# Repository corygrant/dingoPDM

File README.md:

## dingoPDM
dingoPDM is an Infineon Profet based Power Distribution Module. 

# [**Documentation**](https://corygrant.github.io/dingoElec/dingopdm/introduction/)

# [**Store**](https://dingo-electronics.square.site/product/dingopdm/1)

## Disclaimer
Please note that this product has been designed by a hobbyist, not a professional. It is intended for off-road and testing use only. Users should operate the product at their own discretion and risk. The designer explicitly disclaims any responsibility for damage or injury that may result from the use of this product.

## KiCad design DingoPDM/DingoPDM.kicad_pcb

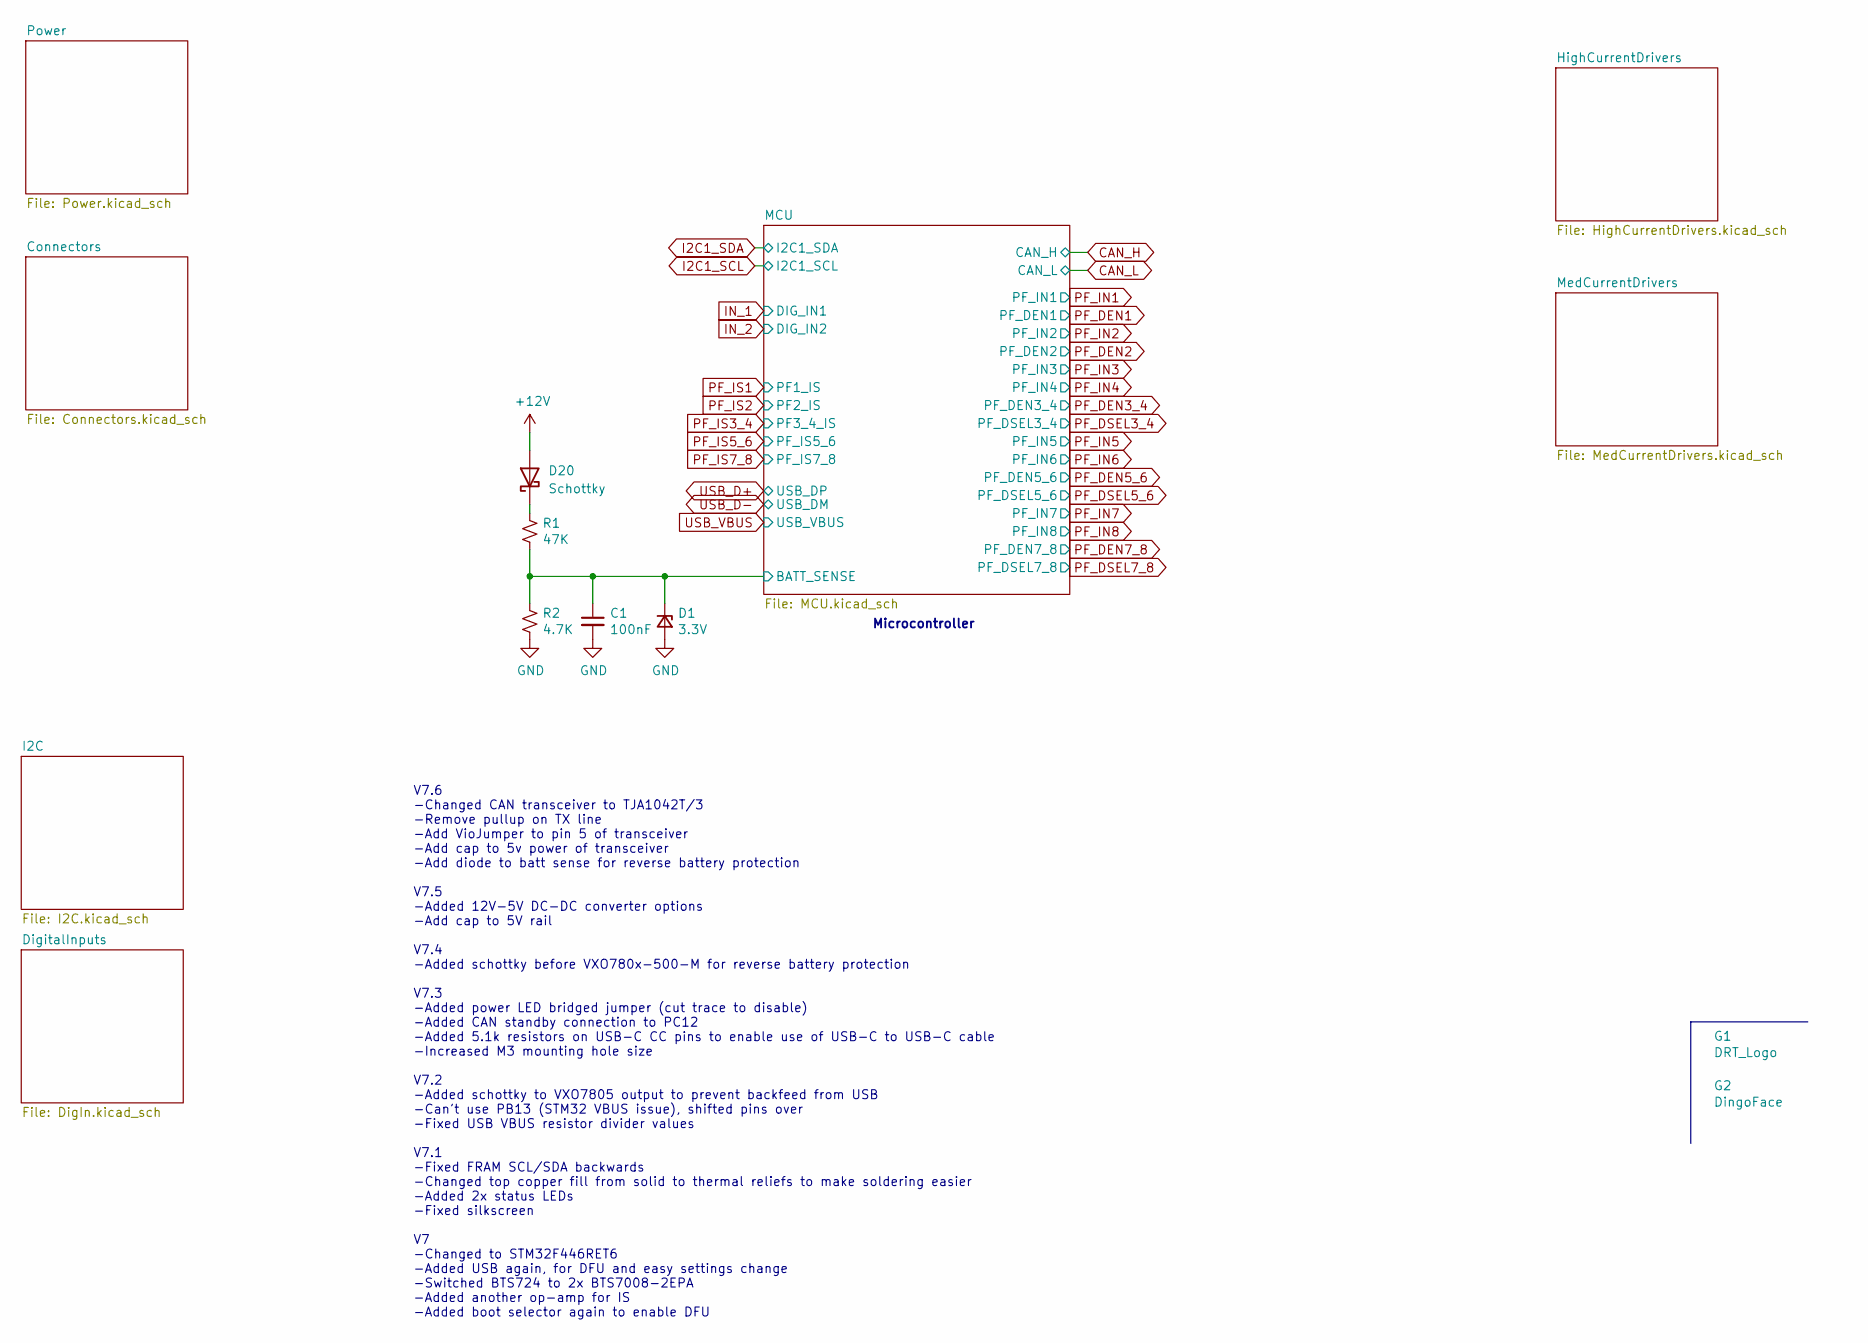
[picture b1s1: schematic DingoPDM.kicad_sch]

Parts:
C1: 100nF; C_0805_2012Metric; Digi-Key_PN 478-1395-1-ND
D1: 3.3V; D_SOD-323_HandSoldering; Digi-Key_PN 1727-5150-1-ND
D20: Schottky; D_SOD-123; Digi-Key_PN 1727-2394-1-ND
G1: DRT_Logo; DRTLogo
G2: DingoFace; DingoFaceNoFill
R1: 47K; R_0805_2012Metric; Digi-Key_PN 311-47.0KCRCT-ND
R2: 4.7K; R_0805_2012Metric; Digi-Key_PN 311-4.70KCRCT-ND

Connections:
+12V: D20.2 (A); also elsewhere on the board
/MCU/BATT_SENSE: C1.1, D1.1 (K), R1.2, R2.1; also elsewhere on the board
GND: C1.2, D1.2 (A), R2.2; also elsewhere on the board
unnamed: D20.1 (K), R1.1

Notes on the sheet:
Microcontroller
V7.6 -Changed CAN transceiver to TJA1042T/3 -Remove pullup on TX line -Add VioJumper to pin 5 of transceiver -Add cap to 5v power of transceiver -Add diode to batt sense for reverse battery protection V7.5 -Added 12V-5V DC-DC converter options -Add cap to 5V rail V7.4 -Added schottky before VXO780x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

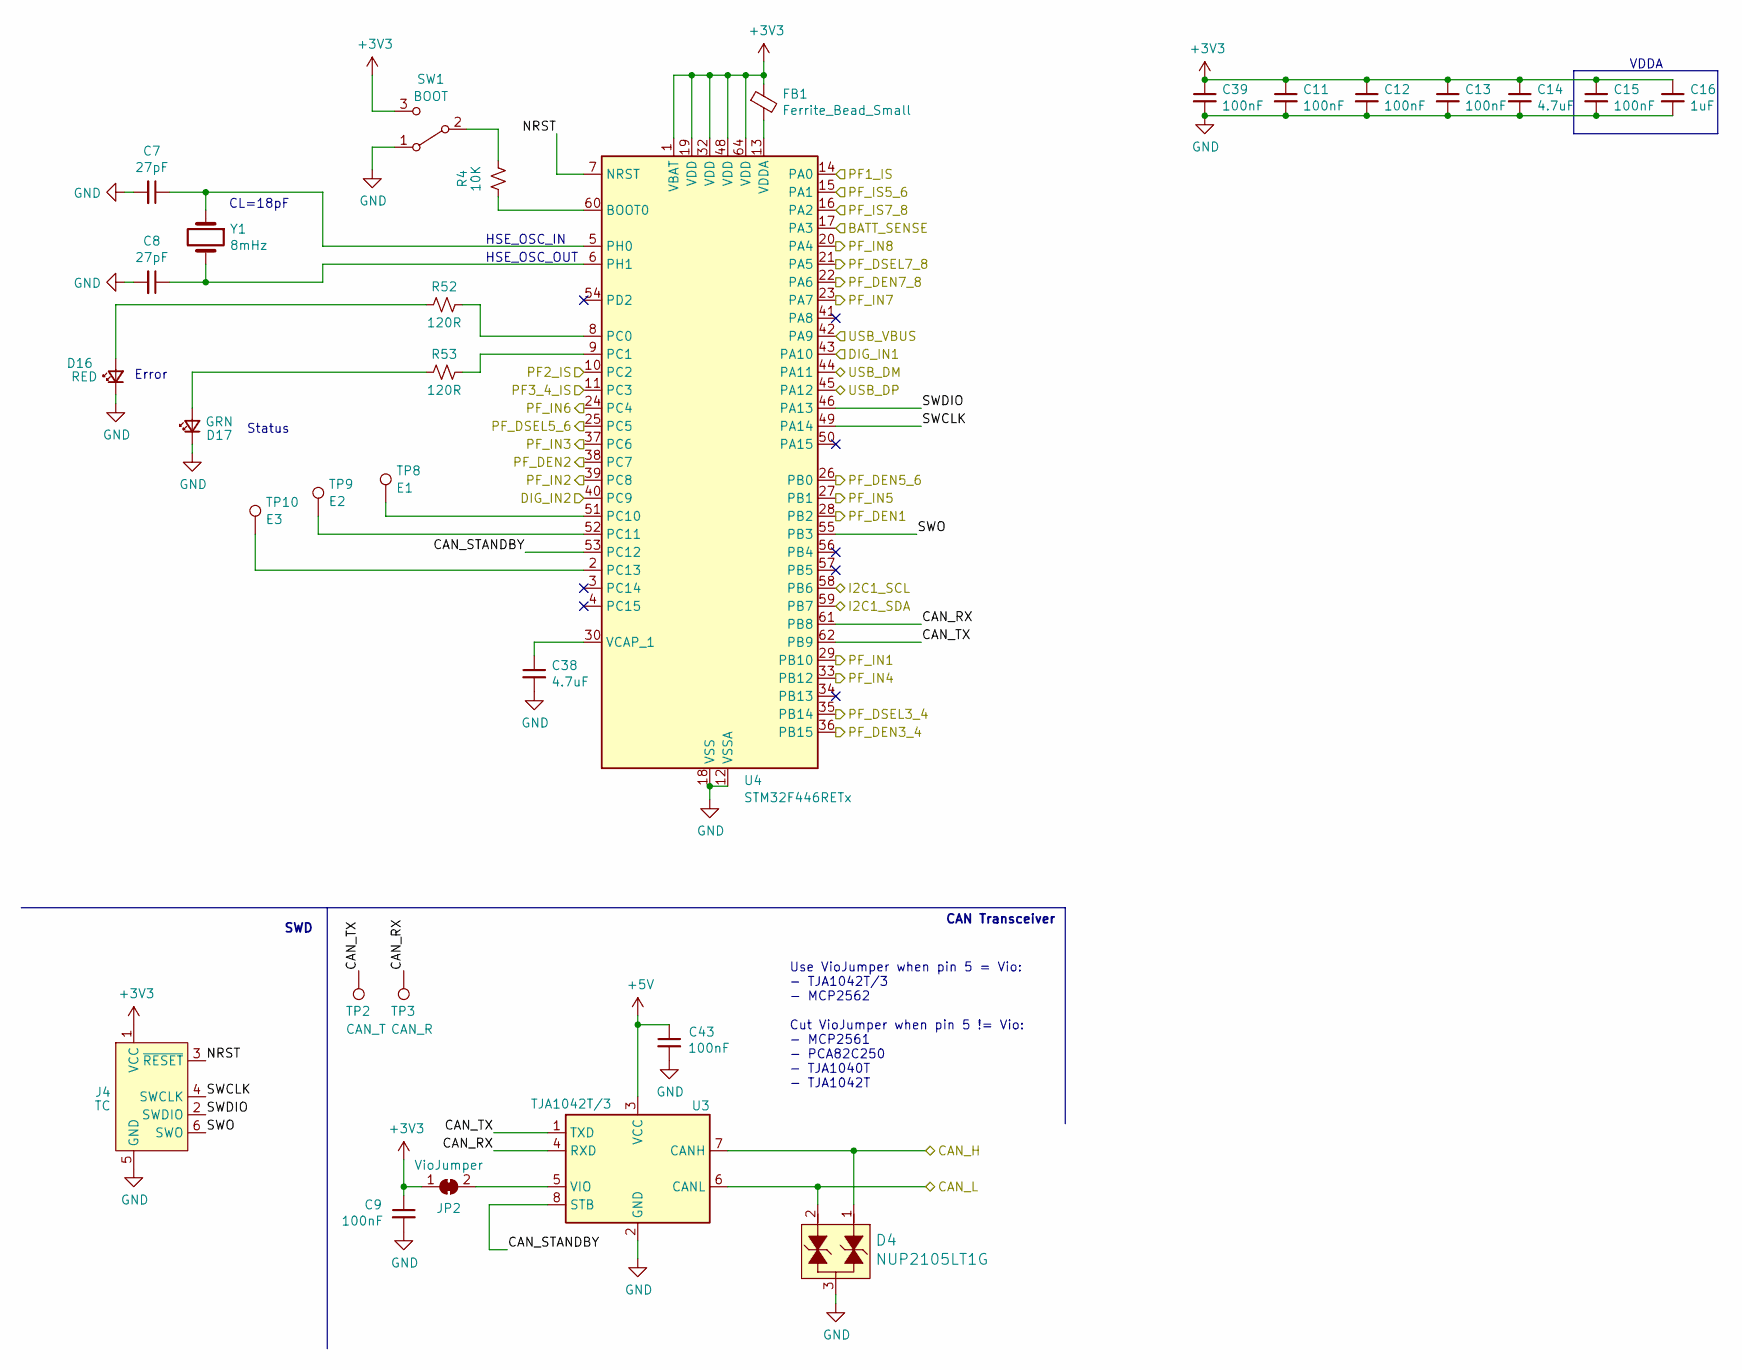
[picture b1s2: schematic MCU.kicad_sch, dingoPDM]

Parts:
C7, C8: 27pF; C_0805_2012Metric; Digi-Key_PN 478-10518-1-ND
C9, C11, C12, C13, C15, C39, C43: 100nF; C_0805_2012Metric; Digi-Key_PN 478-1395-1-ND
C14, C38: 4.7uF; C_0805_2012Metric; Digi-Key_PN 1276-2873-1-ND
C16: 1uF; C_0805_2012Metric; Digi-Key_PN 311-1365-1-ND
D4: NUP2105LT1G; SOT-23-3; Digi-Key_PN NUP2105LT1GOSCT-ND
D16: RED; LED_0805_2012Metric; Digi-Key_PN 475-1278-1-ND
D17: GRN; LED_0805_2012Metric; Digi-Key_PN 475-1410-1-ND
FB1: Ferrite_Bead_Small; R_0805_2012Metric; Digi-Key_PN 490-1054-1-ND
J4: TC; Tag-Connect_TC2030-IDC-NL_2x03_P1.27mm_Vertical
JP2: VioJumper; SolderJumper-2_P1.3mm_Bridged_RoundedPad1.0x1.5mm
R4: 10K; R_0805_2012Metric; Digi-Key_PN 311-10.0KCRDKR-ND
R52, R53: 120R; R_0805_2012Metric; Digi-Key_PN 311-120CRCT-ND
SW1: BOOT; CJS-1200TB; Digi-Key_PN 563-CJS-1200TB1CT-ND
TP2: CAN_T; TestPoint_Keystone_5000-5004_Miniature
TP3: CAN_R; TestPoint_Keystone_5000-5004_Miniature
TP8: E1; TestPoint_Keystone_5000-5004_Miniature
TP9: E2; TestPoint_Keystone_5000-5004_Miniature
TP10: E3; TestPoint_Keystone_5000-5004_Miniature
U3: TJA1042T/3; SOIC-8_3.9x4.9mm_P1.27mm; Digi-Key_PN 568-12625-1-ND
U4: STM32F446RETx; LQFP-64_10x10mm_P0.5mm; Digi-Key_PN 497-15376-ND
Y1: 8mHz; Crystal_SMD_5032-2Pin_5.0x3.2mm_HandSoldering; Digi-Key_PN 535-10630-1-ND

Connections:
+3V3: C9.1, C11.1, C12.1, C13.1, C14.1, C15.1, C16.1, C39.1, FB1.1, J4.1 (VCC), JP2.1 (A), SW1.3 (C), U4.1 (VBAT), U4.19 (VDD), U4.32 (VDD), U4.48 (VDD), U4.64 (VDD); also elsewhere on the board
+5V: C43.1, U3.3 (VCC); also elsewhere on the board
/MCU/BATT_SENSE: U4.17 (PA3); also elsewhere on the board
/MCU/CAN_RX: TP3.1, U3.4 (RXD), U4.61 (PB8)
/MCU/CAN_STANDBY: U3.8 (STB), U4.53 (PC12)
/MCU/CAN_TX: TP2.1, U3.1 (TXD), U4.62 (PB9)
/MCU/NRST: J4.3 (~RESET), U4.7 (NRST)
/MCU/SWCLK: J4.4 (SWCLK), U4.49 (PA14)
/MCU/SWDIO: J4.2 (SWDIO), U4.46 (PA13)
/MCU/SWO: J4.6 (SWO), U4.55 (PB3)
CAN_H: D4.1, U3.7 (CANH); also elsewhere on the board
CAN_L: D4.2, U3.6 (CANL); also elsewhere on the board
GND: C7.2, C8.2, C9.2, C11.2, C12.2, C13.2, C14.2, C15.2, C16.2, C38.2, C39.2, C43.2, D4.3, D16.1 (K), D17.1 (K), J4.5 (GND), SW1.1 (A), U3.2 (GND), U4.12 (VSSA), U4.18 (VSS), U4.31 (VSS), U4.47 (VSS), U4.63 (VSS); also elsewhere on the board
I2C1_SCL: U4.58 (PB6); also elsewhere on the board
I2C1_SDA: U4.59 (PB7); also elsewhere on the board
IN_1: U4.43 (PA10); also elsewhere on the board
IN_2: U4.40 (PC9); also elsewhere on the board
unnamed: D16.2 (A), R52.2
unnamed: D17.2 (A), R53.2
unnamed: JP2.2 (B), U3.5 (VIO)
unnamed: R4.1, SW1.2 (B)
unnamed: R4.2, U4.60 (BOOT0)
unnamed: R52.1, U4.8 (PC0)
unnamed: R53.1, U4.9 (PC1)
unnamed: TP8.1, U4.51 (PC10)
unnamed: TP9.1, U4.52 (PC11)
unnamed: TP10.1, U4.2 (PC13)
unnamed: C7.1, U4.5 (PH0), Y1.1
unnamed: C8.1, U4.6 (PH1), Y1.2
unnamed: C38.1, U4.30 (VCAP_1)
unnamed: FB1.2, U4.13 (VDDA)
PF_DEN1: U4.28 (PB2); also elsewhere on the board
PF_DEN2: U4.38 (PC7); also elsewhere on the board
PF_DEN3_4: U4.36 (PB15); also elsewhere on the board
PF_DEN5_6: U4.26 (PB0); also elsewhere on the board
PF_DEN7_8: U4.22 (PA6); also elsewhere on the board
PF_DSEL3_4: U4.35 (PB14); also elsewhere on the board
PF_DSEL5_6: U4.25 (PC5); also elsewhere on the board
PF_DSEL7_8: U4.21 (PA5); also elsewhere on the board
PF_IN1: U4.29 (PB10); also elsewhere on the board
PF_IN2: U4.39 (PC8); also elsewhere on the board
PF_IN3: U4.37 (PC6); also elsewhere on the board
PF_IN4: U4.33 (PB12); also elsewhere on the board
PF_IN5: U4.27 (PB1); also elsewhere on the board
PF_IN6: U4.24 (PC4); also elsewhere on the board
PF_IN7: U4.23 (PA7); also elsewhere on the board
PF_IN8: U4.20 (PA4); also elsewhere on the board
PF_IS1: U4.14 (PA0); also elsewhere on the board
PF_IS2: U4.10 (PC2); also elsewhere on the board
PF_IS3_4: U4.11 (PC3); also elsewhere on the board
PF_IS5_6: U4.15 (PA1); also elsewhere on the board
PF_IS7_8: U4.16 (PA2); also elsewhere on the board
USB_D+: U4.45 (PA12); also elsewhere on the board
USB_D-: U4.44 (PA11); also elsewhere on the board
USB_VBUS: U4.42 (PA9); also elsewhere on the board

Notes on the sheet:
Use VioJumper when pin 5 = Vio: - TJA1042T/3 - MCP2562 Cut VioJumper when pin 5 != Vio: - MCP2561 - PCA82C250 - TJA1040T - TJA1042T
SWD
Error
CAN Transceiver
HSE_OSC_IN
CL=18pF
HSE_OSC_OUT
VDDA
Status

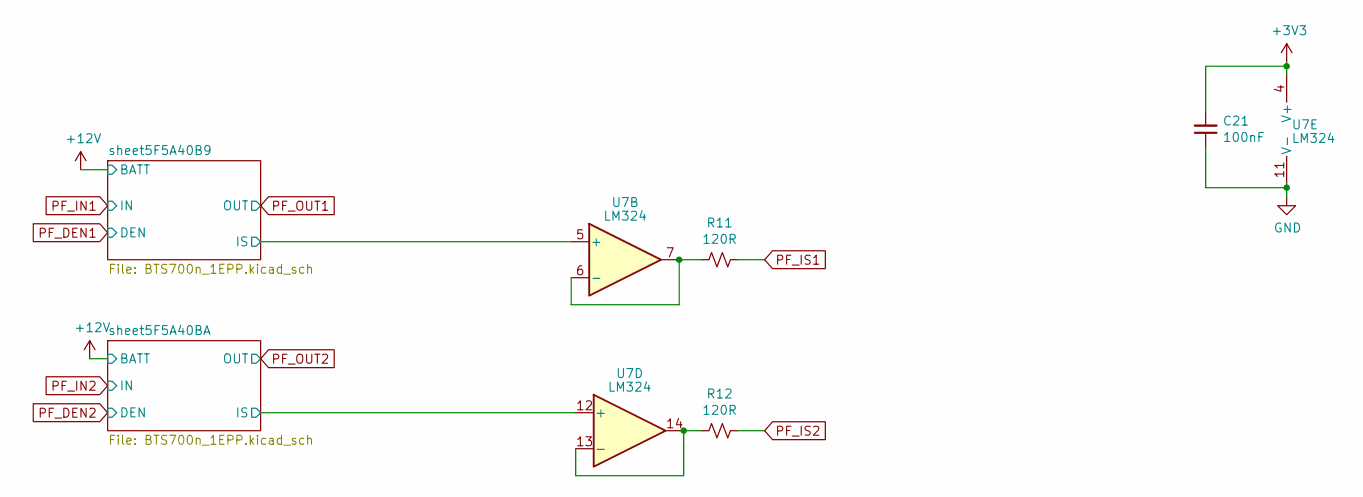
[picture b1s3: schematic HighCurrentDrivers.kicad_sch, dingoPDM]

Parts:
C21: 100nF; C_0805_2012Metric; Digi-Key_PN 478-1395-1-ND
R11, R12: 120R; R_0805_2012Metric; Digi-Key_PN 311-120CRCT-ND
U7: LM324; TSSOP-14_4.4x5mm_P0.65mm; Digi-Key_PN 497-7330-1-ND

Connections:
+3V3: C21.2, U7.4 (V+); also elsewhere on the board
/HighCurrentDrivers/sheet5F5A40B9/IS: U7.5 (+); also elsewhere on the board
/HighCurrentDrivers/sheet5F5A40BA/IS: U7.12 (+); also elsewhere on the board
GND: C21.1, U7.11 (V-); also elsewhere on the board
unnamed: R11.2, U7.6 (-), U7.7
unnamed: R12.2, U7.13 (-), U7.14
PF_IS1: R11.1; also elsewhere on the board
PF_IS2: R12.1; also elsewhere on the board

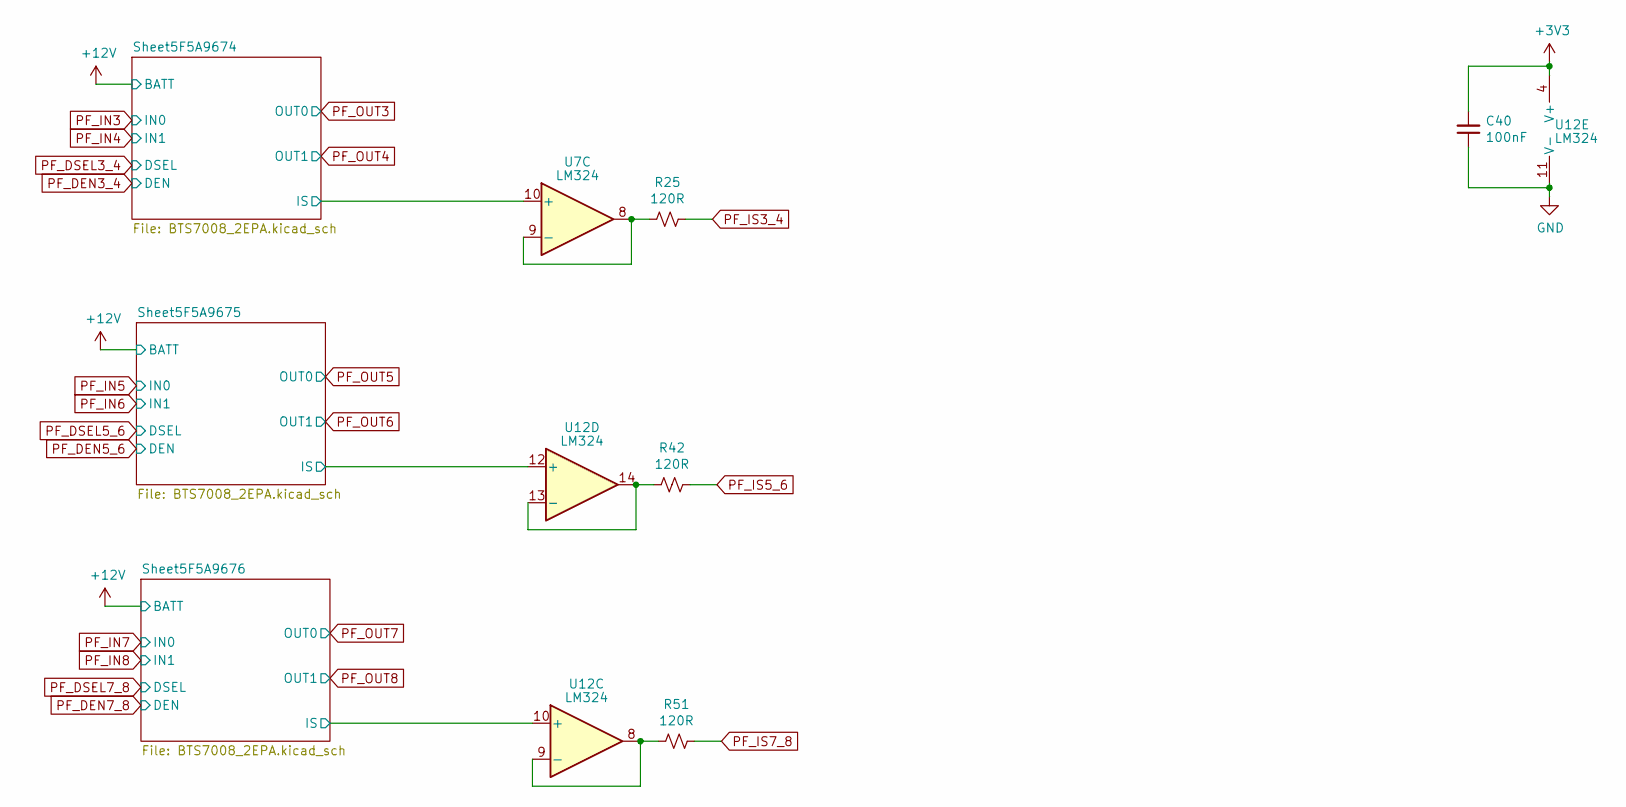
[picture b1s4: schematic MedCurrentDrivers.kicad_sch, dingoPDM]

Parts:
C40: 100nF; C_0805_2012Metric; Digi-Key_PN 478-1395-1-ND
R25, R42, R51: 120R; R_0805_2012Metric; Digi-Key_PN 311-120CRCT-ND
U7, U12: LM324; TSSOP-14_4.4x5mm_P0.65mm; Digi-Key_PN 497-7330-1-ND

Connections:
+3V3: C40.2, U12.4 (V+); also elsewhere on the board
/MedCurrentDrivers/Sheet5F5A9674/IS: U7.10 (+); also elsewhere on the board
/MedCurrentDrivers/Sheet5F5A9675/IS: U12.12 (+); also elsewhere on the board
/MedCurrentDrivers/Sheet5F5A9676/IS: U12.10 (+); also elsewhere on the board
GND: C40.1, U12.11 (V-); also elsewhere on the board
unnamed: R25.2, U7.8, U7.9 (-)
unnamed: R51.2, U12.8, U12.9 (-)
unnamed: R42.2, U12.13 (-), U12.14
PF_IS3_4: R25.1; also elsewhere on the board
PF_IS5_6: R42.1; also elsewhere on the board
PF_IS7_8: R51.1; also elsewhere on the board

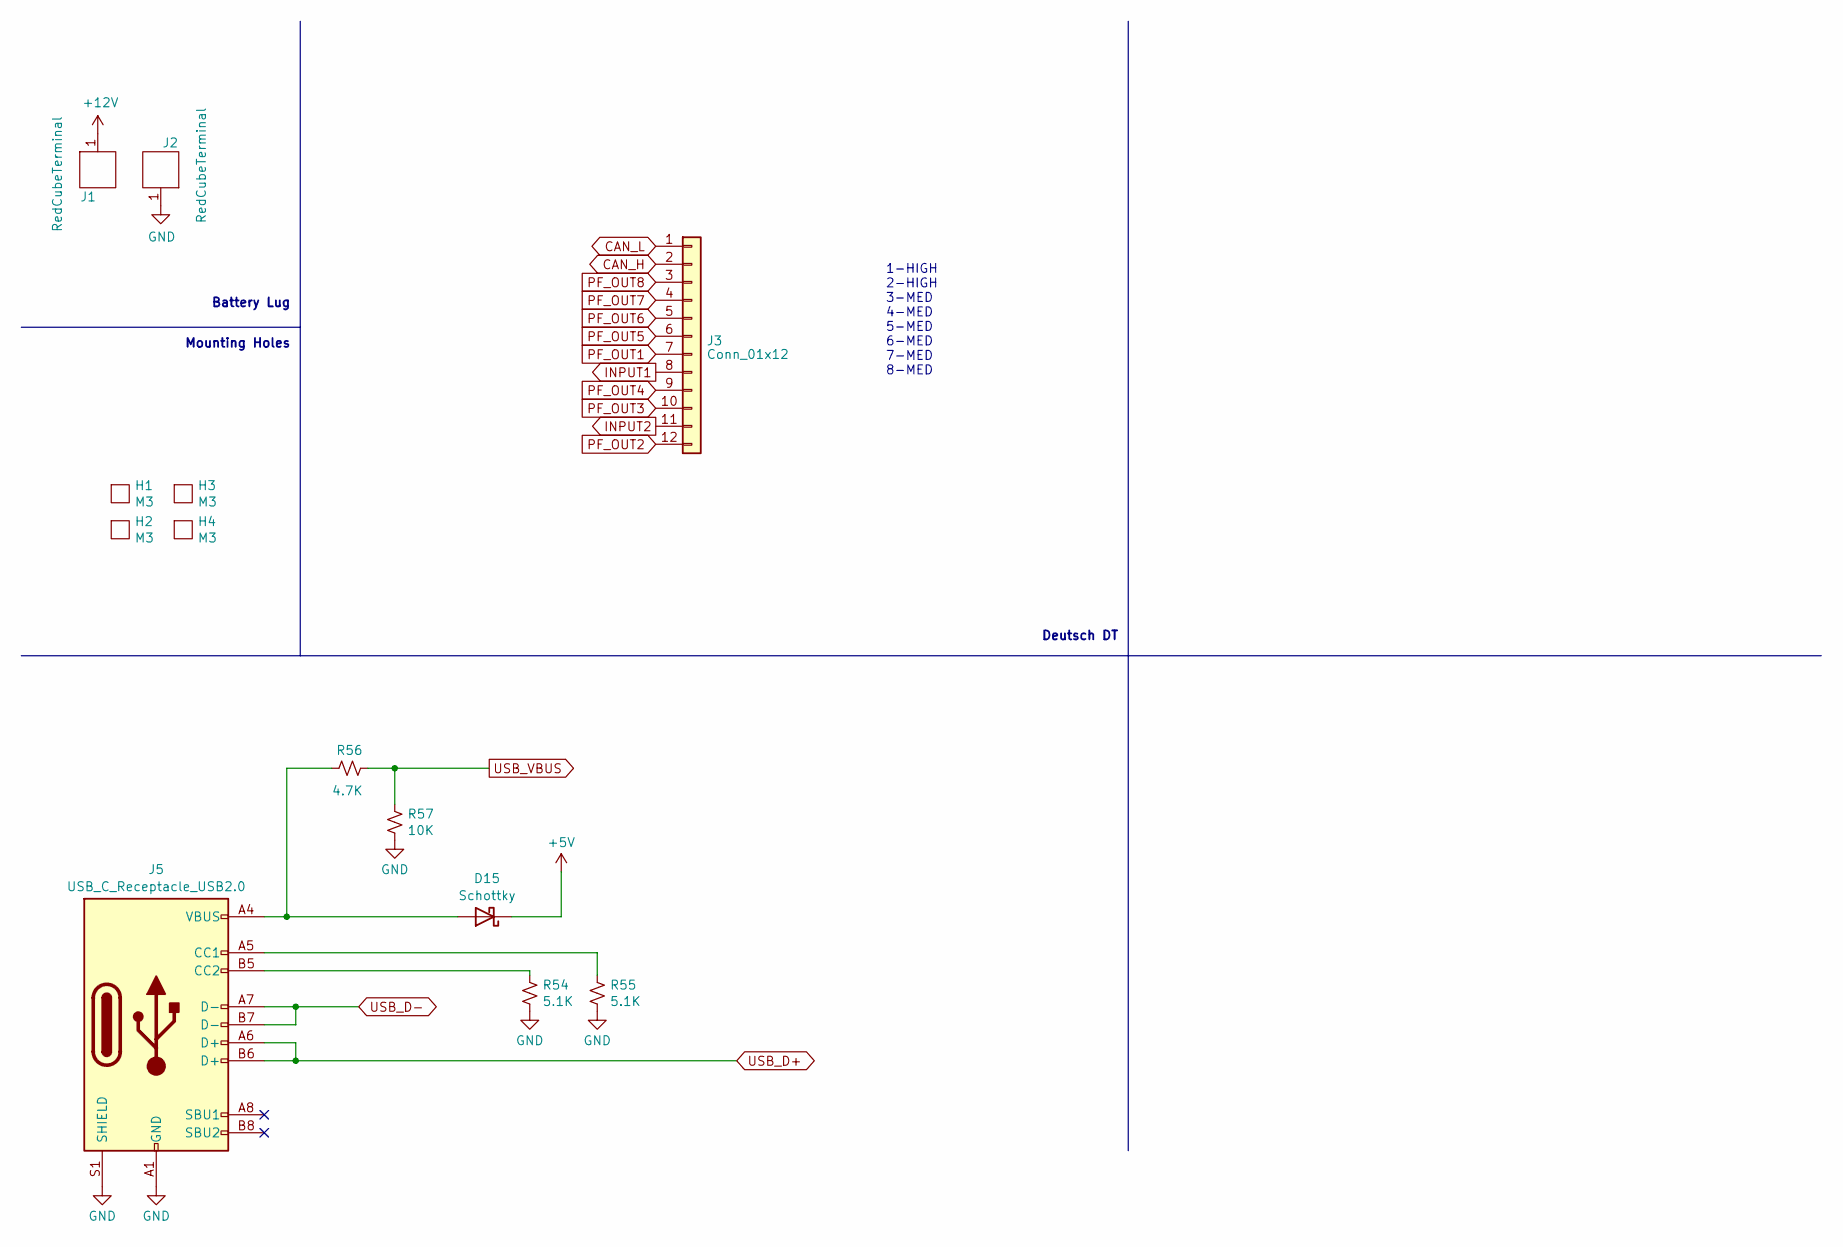
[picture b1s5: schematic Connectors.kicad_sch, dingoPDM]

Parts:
D15: Schottky; D_SOD-123; Digi-Key_PN 1727-2394-1-ND
H1, H2, H3, H4: M3; MountingHole_3.2mm_M3_ISO7380_Pad
J1, J2: RedCubeTerminal; M6_Hole_8Pin_7461084; Digi-Key_PN 732-3203-ND
J3: Conn_01x12; DT15-12PA; LCSC C5341788
J5: USB_C_Receptacle_USB2.0; USB_C_Receptacle_GCT_USB4085; Digi-Key_PN 2073-USB4085-GF-ACT-ND
R54, R55: 5.1K; R_0805_2012Metric; Digi-Key_PN 311-5.1KARCT-ND
R56: 4.7K; R_0805_2012Metric; Digi-Key_PN 311-4.70KCRCT-ND
R57: 10K; R_0805_2012Metric; Digi-Key_PN 311-10.0KCRDKR-ND

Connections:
+5V: D15.1 (K); also elsewhere on the board
+12V: J1.1; also elsewhere on the board
CAN_H: J3.2; also elsewhere on the board
CAN_L: J3.1; also elsewhere on the board
GND: J2.1, J5.A1 (GND), J5.A12 (GND), J5.B1 (GND), J5.B12 (GND), J5.S1 (SHIELD), R54.2, R55.2, R57.2; also elsewhere on the board
INPUT1: J3.8; also elsewhere on the board
INPUT2: J3.11; also elsewhere on the board
unnamed: D15.2 (A), J5.A4 (VBUS), J5.A9 (VBUS), J5.B4 (VBUS), J5.B9 (VBUS), R56.1
unnamed: J5.A5 (CC1), R55.1
unnamed: J5.B5 (CC2), R54.1
PF_OUT1: J3.7; also elsewhere on the board
PF_OUT2: J3.12; also elsewhere on the board
PF_OUT3: J3.10; also elsewhere on the board
PF_OUT4: J3.9; also elsewhere on the board
PF_OUT5: J3.6; also elsewhere on the board
PF_OUT6: J3.5; also elsewhere on the board
PF_OUT7: J3.4; also elsewhere on the board
PF_OUT8: J3.3; also elsewhere on the board
USB_D+: J5.A6 (D+), J5.B6 (D+); also elsewhere on the board
USB_D-: J5.A7 (D-), J5.B7 (D-); also elsewhere on the board
USB_VBUS: R56.2, R57.1; also elsewhere on the board

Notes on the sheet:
1-HIGH 2-HIGH 3-MED 4-MED 5-MED 6-MED 7-MED 8-MED
Deutsch DT
Battery Lug
Mounting Holes

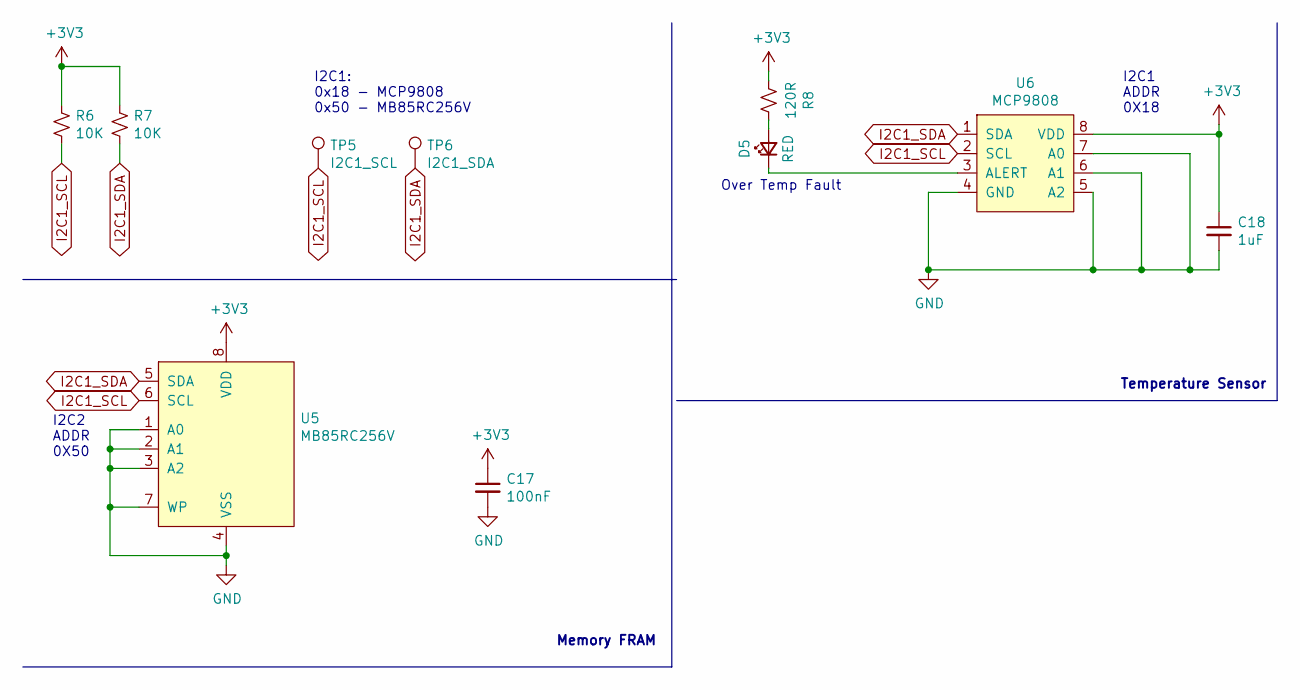
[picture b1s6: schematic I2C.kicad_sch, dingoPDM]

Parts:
C17: 100nF; C_0805_2012Metric; Digi-Key_PN 478-1395-1-ND
C18: 1uF; C_0805_2012Metric; Digi-Key_PN 311-1365-1-ND
D5: RED; LED_0805_2012Metric; Digi-Key_PN 475-1278-1-ND
R6, R7: 10K; R_0805_2012Metric; Digi-Key_PN 311-10.0KCRDKR-ND
R8: 120R; R_0805_2012Metric; Digi-Key_PN 311-120CRCT-ND
TP5: I2C1_SCL; TestPoint_Keystone_5000-5004_Miniature
TP6: I2C1_SDA; TestPoint_Keystone_5000-5004_Miniature
U5: MB85RC256V; SOIC-8_3.9x4.9mm_P1.27mm; Digi-Key_PN 865-1261-1-ND
U6: MCP9808; MSOP-8_3x3mm_P0.65mm; Digi-Key_PN MCP9808T-E/MSCT-ND

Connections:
+3V3: C17.1, C18.1, R6.1, R7.1, R8.2, U5.8 (VDD), U6.8 (VDD); also elsewhere on the board
GND: C17.2, C18.2, U5.1 (A0), U5.2 (A1), U5.3 (A2), U5.4 (VSS), U5.7 (WP), U6.4 (GND), U6.5 (A2), U6.6 (A1), U6.7 (A0); also elsewhere on the board
I2C1_SCL: R6.2, TP5.1, U5.6 (SCL), U6.2 (SCL); also elsewhere on the board
I2C1_SDA: R7.2, TP6.1, U5.5 (SDA), U6.1 (SDA); also elsewhere on the board
unnamed: D5.2 (A), R8.1
unnamed: D5.1 (K), U6.3 (ALERT)

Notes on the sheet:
I2C1 ADDR 0X18
I2C2 ADDR 0X50
Over Temp Fault
Temperature Sensor
I2C1: 0x18 - MCP9808 0x50 - MB85RC256V
Memory FRAM

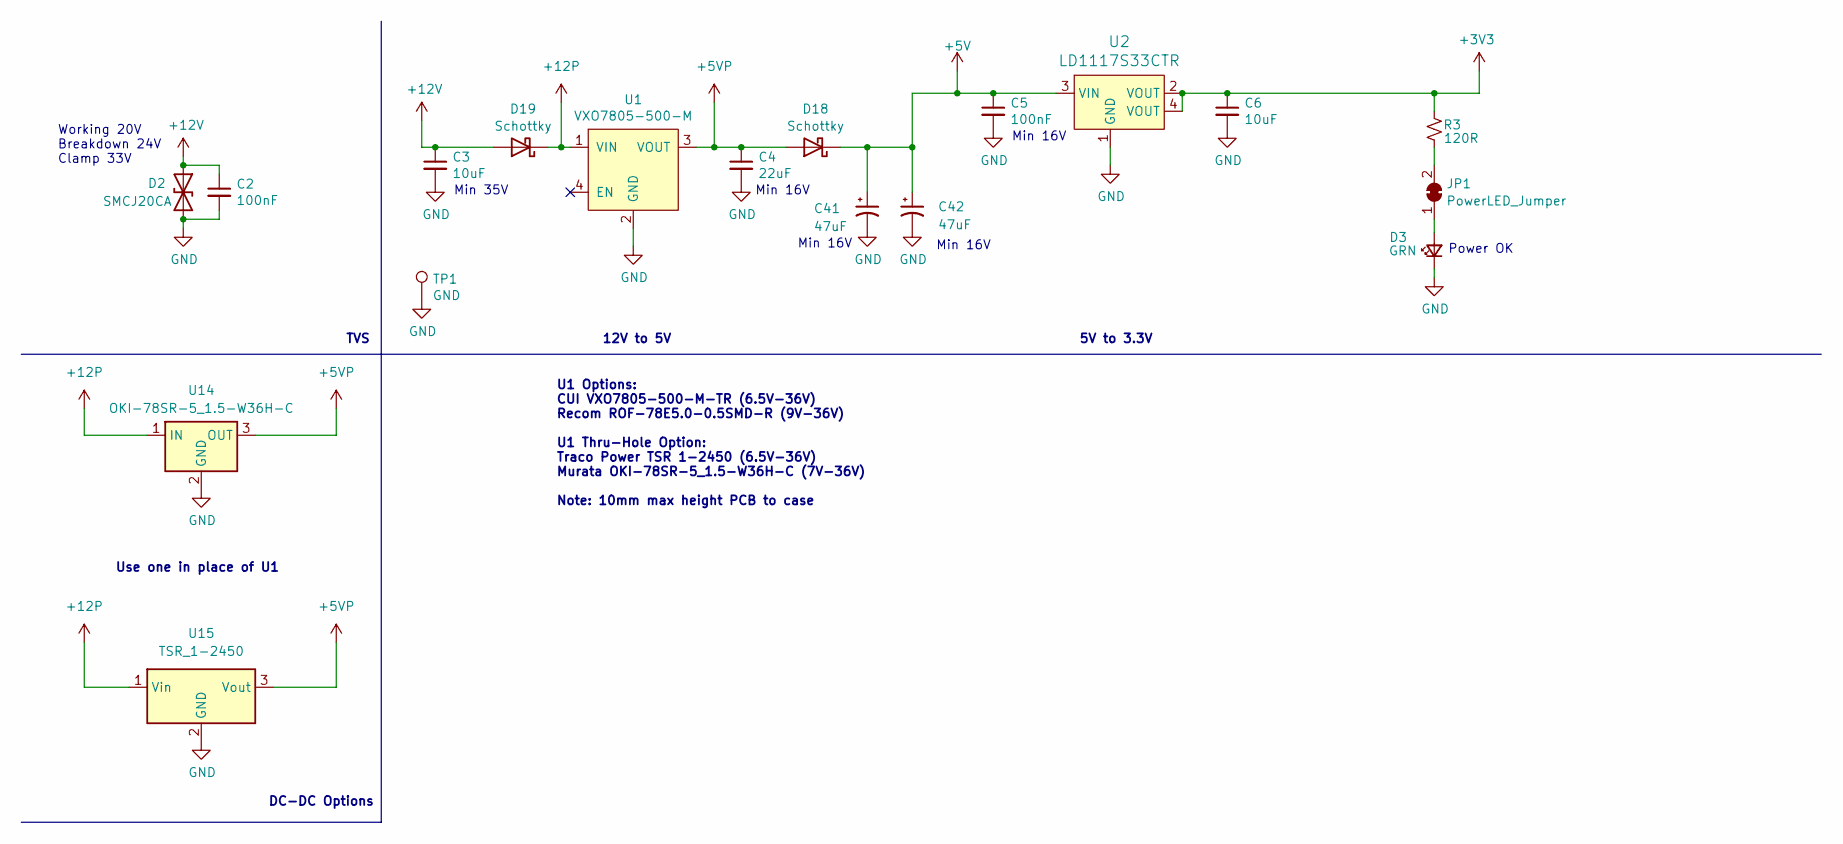
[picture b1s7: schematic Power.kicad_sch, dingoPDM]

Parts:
C2, C5: 100nF; C_0805_2012Metric; Digi-Key_PN 478-1395-1-ND
C3, C6: 10uF; C_0805_2012Metric; Digi-Key_PN 445-11516-1-ND
C4: 22uF; C_0805_2012Metric; Digi-Key_PN 490-10749-1-ND
C41, C42: 47uF; C_2220_5750Metric; Digi-Key_PN 445-7935-1-ND
D2: SMCJ20CA; DO-214AB_TVS; Digi-Key_PN SMCJ20CABCT-ND
D3: GRN; LED_0805_2012Metric; Digi-Key_PN 475-1410-1-ND
D18, D19: Schottky; D_SOD-123; Digi-Key_PN 1727-2394-1-ND
JP1: PowerLED_Jumper; SolderJumper-2_P1.3mm_Bridged_RoundedPad1.0x1.5mm
R3: 120R; R_0805_2012Metric; Digi-Key_PN 311-120CRCT-ND
TP1: GND; TestPoint_Keystone_5000-5004_Miniature
U1: VXO7805-500-M; VXO78x-500-M; Digi-Key_PN 102-VXO7805-500-M-CT-ND
U2: LD1117S33CTR; SOT-223; Digi-Key_PN 497-1241-1-ND
U14: OKI-78SR-5_1.5-W36H-C; Converter_DCDC_Murata_OKI-78SR_Horizontal; Digi-Key_PN 811-2692-ND
U15: TSR_1-2450; Converter_DCDC_TRACO_TSR-1_THT; Digi-Key_PN 1951-2747-ND

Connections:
+3V3: C6.1, R3.2, U2.2 (VOUT), U2.4 (VOUT); also elsewhere on the board
+5V: C5.1, C41.1, C42.1, D18.1 (K), U2.3 (VIN); also elsewhere on the board
+5VP: C4.1, D18.2 (A), U1.3 (VOUT), U14.3 (OUT), U15.3 (Vout)
+12P: D19.1 (K), U1.1 (VIN), U14.1 (IN), U15.1 (Vin)
+12V: C2.1, C3.1, D2.1 (A1), D19.2 (A); also elsewhere on the board
GND: C2.2, C3.2, C4.2, C5.2, C6.2, C41.2, C42.2, D2.2 (A2), D3.1 (K), TP1.1, U1.2 (GND), U2.1 (GND), U14.2 (GND), U15.2 (GND); also elsewhere on the board
unnamed: D3.2 (A), JP1.1 (A)
unnamed: JP1.2 (B), R3.1

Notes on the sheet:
Min 16V
TVS
Min 35V
Power OK
5V to 3.3V
U1 Options: CUI VXO7805-500-M-TR (6.5V-36V) Recom ROF-78E5.0-0.5SMD-R (9V-36V) U1 Thru-Hole Option: Traco Power TSR 1-2450 (6.5V-36V) Murata OKI-78SR-5_1.5-W36H-C (7V-36V) Note: 10mm max height PCB to case
12V to 5V
DC-DC Options
Use one in place of U1
Working 20V Breakdown 24V Clamp 33V

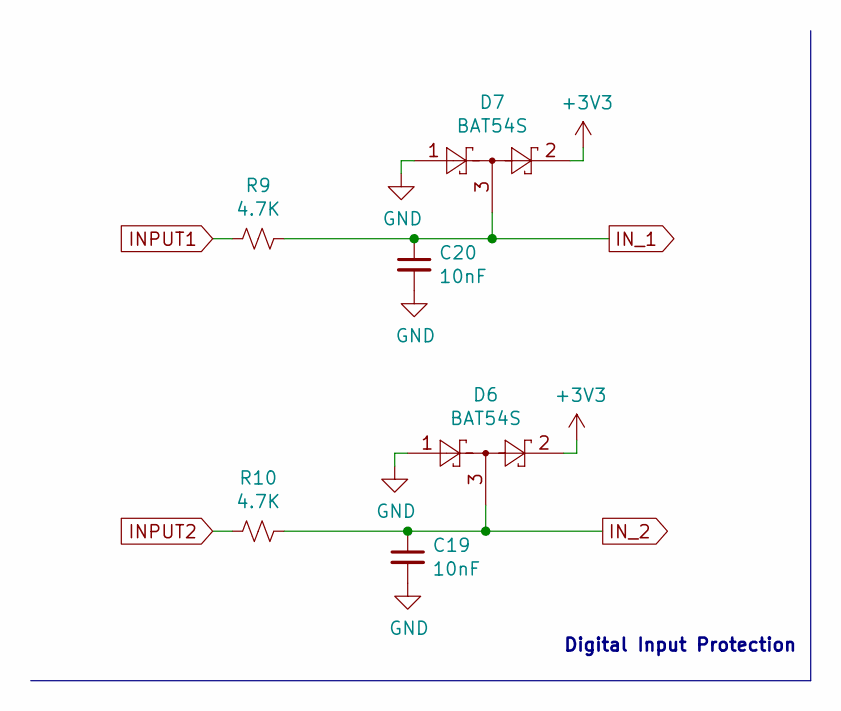
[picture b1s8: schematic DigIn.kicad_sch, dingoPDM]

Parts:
C19, C20: 10nF; C_0805_2012Metric; Digi-Key_PN 311-1136-1-ND
D6, D7: BAT54S; SOT-23; Digi-Key_PN BAT54SLT1GOSCT-ND
R9, R10: 4.7K; R_0805_2012Metric; Digi-Key_PN 311-4.70KCRCT-ND

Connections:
+3V3: D6.2, D7.2; also elsewhere on the board
GND: C19.2, C20.2, D6.1, D7.1; also elsewhere on the board
INPUT1: R9.2; also elsewhere on the board
INPUT2: R10.2; also elsewhere on the board
IN_1: C20.1, D7.3, R9.1; also elsewhere on the board
IN_2: C19.1, D6.3, R10.1; also elsewhere on the board

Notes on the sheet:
Digital Input Protection

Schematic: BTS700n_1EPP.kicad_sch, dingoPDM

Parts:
C22: 47nF; C_0805_2012Metric; Digi-Key_PN 399-1166-1-ND
C23: 100nF; C_0805_2012Metric; Digi-Key_PN 478-1395-1-ND
C24: 10nF; C_0805_2012Metric; Digi-Key_PN 311-1136-1-ND
C25: 220pF; C_0805_2012Metric; Digi-Key_PN 399-1138-1-ND
D8: BYG23M; DO-214AC; Digi-Key_PN BYG23M-E3/TR3GICT-ND
D9: 3.3V; D_SOD-323_HandSoldering; Digi-Key_PN 1727-5150-1-ND
R13, R14, R17, R18: 4.7K; R_0805_2012Metric; Digi-Key_PN 311-4.70KCRCT-ND
R15: 1.2K; R_0805_2012Metric; Digi-Key_PN 311-1.20KCRCT-ND
R16: 47R 1/4W; R_1206_3216Metric; Digi-Key_PN 311-47.0FRCT-ND
U8: BTS700n-1EPP; TDSO-14; Digi-Key_PN BTS70021EPPXUMA1CT-ND

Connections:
+12V: C22.2, C23.2, U8.15 (VS); also elsewhere on the board
/HighCurrentDrivers/sheet5F5A40B9/IS: C25.2, R18.1; also elsewhere on the board
GND: C23.1, C24.1, C25.1, D8.A, D9.2 (A), R15.2, R16.1; also elsewhere on the board
unnamed: D9.1 (K), R17.1, R18.2
unnamed: R14.1, U8.3 (DEN)
unnamed: C22.1, R16.2, U8.1 (GND)
unnamed: R13.1, U8.2 (IN)
unnamed: R15.1, R17.2, U8.4 (IS)
PF_DEN1: R14.2; also elsewhere on the board
PF_IN1: R13.2; also elsewhere on the board
PF_OUT1: C24.2, D8.K, U8.8 (OUT1), U8.9 (OUT2), U8.10 (OUT3), U8.11 (NC4), U8.12 (OUT4), U8.13 (OUT5), U8.14 (OUT6); also elsewhere on the board

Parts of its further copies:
C26: 47nF; C_0805_2012Metric; Digi-Key_PN 399-1166-1-ND
C27: 100nF; C_0805_2012Metric; Digi-Key_PN 478-1395-1-ND
C28: 10nF; C_0805_2012Metric; Digi-Key_PN 311-1136-1-ND
C29: 220pF; C_0805_2012Metric; Digi-Key_PN 399-1138-1-ND
D10: BYG23M; DO-214AC; Digi-Key_PN BYG23M-E3/TR3GICT-ND
D11: 3.3V; D_SOD-323_HandSoldering; Digi-Key_PN 1727-5150-1-ND
R19, R20, R23, R24: 4.7K; R_0805_2012Metric; Digi-Key_PN 311-4.70KCRCT-ND
R21: 1.2K; R_0805_2012Metric; Digi-Key_PN 311-1.20KCRCT-ND
R22: 47R 1/4W; R_1206_3216Metric; Digi-Key_PN 311-47.0FRCT-ND
U9: BTS700n-1EPP; TDSO-14; Digi-Key_PN BTS70021EPPXUMA1CT-ND

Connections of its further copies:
+12V: C26.2, C27.2, U9.15 (VS); also elsewhere on the board
/HighCurrentDrivers/sheet5F5A40BA/IS: C29.2, R24.1; also elsewhere on the board
GND: C27.1, C28.1, C29.1, D10.A, D11.2 (A), R21.2, R22.1; also elsewhere on the board
unnamed: D11.1 (K), R23.1, R24.2
unnamed: R20.1, U9.3 (DEN)
unnamed: C26.1, R22.2, U9.1 (GND)
unnamed: R19.1, U9.2 (IN)
unnamed: R21.1, R23.2, U9.4 (IS)
PF_DEN2: R20.2; also elsewhere on the board
PF_IN2: R19.2; also elsewhere on the board
PF_OUT2: C28.2, D10.K, U9.8 (OUT1), U9.9 (OUT2), U9.10 (OUT3), U9.11 (NC4), U9.12 (OUT4), U9.13 (OUT5), U9.14 (OUT6); also elsewhere on the board

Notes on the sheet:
RC Filter
Flyback

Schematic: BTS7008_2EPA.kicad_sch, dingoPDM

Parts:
C10: 47nF; C_0805_2012Metric; Digi-Key_PN 399-1166-1-ND
C33: 100nF; C_0805_2012Metric; Digi-Key_PN 478-1395-1-ND
C34: 220pF; C_0805_2012Metric; Digi-Key_PN 399-1138-1-ND
D13: 3.3V; D_SOD-323_HandSoldering; Digi-Key_PN 1727-5150-1-ND
R34, R35, R36, R37, R40, R41: 4.7K; R_0805_2012Metric; Digi-Key_PN 311-4.70KCRCT-ND
R38: 1.2K; R_0805_2012Metric; Digi-Key_PN 311-1.20KCRCT-ND
R39: 47R 1/4W; R_1206_3216Metric; Digi-Key_PN 311-47.0FRCT-ND
U10: BTS7008-2EPA; TDSO-14; Digi-Key_PN BTS70082EPAXUMA1CT-ND

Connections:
+12V: C10.2, C33.2, U10.15 (VS); also elsewhere on the board
/MedCurrentDrivers/Sheet5F5A9675/IS: C34.2, R41.1; also elsewhere on the board
GND: C33.1, C34.1, D13.2 (A), R38.2, R39.1; also elsewhere on the board
unnamed: D13.1 (K), R40.1, R41.2
unnamed: R35.1, U10.3 (DEN)
unnamed: R36.2, U10.5 (DSEL)
unnamed: C10.1, R39.2, U10.1 (GND)
unnamed: R34.1, U10.2 (IN0)
unnamed: R37.1, U10.6 (IN1)
unnamed: R38.1, R40.2, U10.4 (IS)
PF_DEN5_6: R35.2; also elsewhere on the board
PF_DSEL5_6: R36.1; also elsewhere on the board
PF_IN5: R34.2; also elsewhere on the board
PF_IN6: R37.2; also elsewhere on the board
PF_OUT5: U10.12 (OUT0), U10.13 (OUT0), U10.14 (OUT0); also elsewhere on the board
PF_OUT6: U10.8 (OUT1), U10.9 (OUT1), U10.10 (OUT1); also elsewhere on the board

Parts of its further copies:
C30, C35: 47nF; C_0805_2012Metric; Digi-Key_PN 399-1166-1-ND
C31, C36: 100nF; C_0805_2012Metric; Digi-Key_PN 478-1395-1-ND
C32, C37: 220pF; C_0805_2012Metric; Digi-Key_PN 399-1138-1-ND
D12, D14: 3.3V; D_SOD-323_HandSoldering; Digi-Key_PN 1727-5150-1-ND
R26, R27, R28, R29, R32, R33, R43, R44, R45, R46, R49, R50: 4.7K; R_0805_2012Metric; Digi-Key_PN 311-4.70KCRCT-ND
R30, R47: 1.2K; R_0805_2012Metric; Digi-Key_PN 311-1.20KCRCT-ND
R31, R48: 47R 1/4W; R_1206_3216Metric; Digi-Key_PN 311-47.0FRCT-ND
U11, U13: BTS7008-2EPA; TDSO-14; Digi-Key_PN BTS70082EPAXUMA1CT-ND

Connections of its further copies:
+12V: C30.2, C31.2, C35.2, C36.2, U11.15 (VS), U13.15 (VS); also elsewhere on the board
/MedCurrentDrivers/Sheet5F5A9674/IS: C32.2, R33.1; also elsewhere on the board
/MedCurrentDrivers/Sheet5F5A9676/IS: C37.2, R50.1; also elsewhere on the board
GND: C31.1, C32.1, C36.1, C37.1, D12.2 (A), D14.2 (A), R30.2, R31.1, R47.2, R48.1; also elsewhere on the board
unnamed: D12.1 (K), R32.1, R33.2
unnamed: D14.1 (K), R49.1, R50.2
unnamed: R27.1, U11.3 (DEN)
unnamed: R28.2, U11.5 (DSEL)
unnamed: C30.1, R31.2, U11.1 (GND)
unnamed: R26.1, U11.2 (IN0)
unnamed: R29.1, U11.6 (IN1)
unnamed: R30.1, R32.2, U11.4 (IS)
unnamed: R44.1, U13.3 (DEN)
unnamed: R45.2, U13.5 (DSEL)
unnamed: C35.1, R48.2, U13.1 (GND)
unnamed: R43.1, U13.2 (IN0)
unnamed: R46.1, U13.6 (IN1)
unnamed: R47.1, R49.2, U13.4 (IS)
PF_DEN3_4: R27.2; also elsewhere on the board
PF_DEN7_8: R44.2; also elsewhere on the board
PF_DSEL3_4: R28.1; also elsewhere on the board
PF_DSEL7_8: R45.1; also elsewhere on the board
PF_IN3: R26.2; also elsewhere on the board
PF_IN4: R29.2; also elsewhere on the board
PF_IN7: R43.2; also elsewhere on the board
PF_IN8: R46.2; also elsewhere on the board
PF_OUT3: U11.12 (OUT0), U11.13 (OUT0), U11.14 (OUT0); also elsewhere on the board
PF_OUT4: U11.8 (OUT1), U11.9 (OUT1), U11.10 (OUT1); also elsewhere on the board
PF_OUT7: U13.12 (OUT0), U13.13 (OUT0), U13.14 (OUT0); also elsewhere on the board
PF_OUT8: U13.8 (OUT1), U13.9 (OUT1), U13.10 (OUT1); also elsewhere on the board

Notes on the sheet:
RC Filter
